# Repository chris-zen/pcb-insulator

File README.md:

# PCB Insulator

This project contains the design ideas to build a PCB insulator using UV LEDS.

The design is for a board of 100x75 mm, but you can compose several boards to increase the exposure surface. Just remember that you will need to use the appropriate power supply. I include some numbers to help with this.

# Numbers per board

LED specs: 3.3V 20mA

Voltage across resistor = 12V - (3 * 3.2V) = 2.4V

Resistor value = 2.4V / 0.02A = 120 Ohm

Power dissipated by resistor = 2.4V * 0.02A = 0.048 W = 48 mW

Power consumed by LED = 3.2V * 0.02A = 0.064W = 64mW

1 Board contains 16 resistors and 48 LEDs

Total power dissipated by resistors = 16 * 0.048W = 0.768W

Total power consumed by LEDs = 48 * 0.064W = 3.072W

**Total power = 0.768W + 3.072W = 3.84W**

**Total current consumption = 3.84W / 12V = 0.32A**

If you compose 4 boards you would need a power supply supporting 15.36W and 1.28A

# References

I have based my design on those other projects:

- http://www.instructables.com/id/Arduino-controlled-UV-LED-PCB-Exposure-Box/?ALLSTEPS
- http://www.carlolog.net/log/2012/09/making-an-uv-exposure-box-from-scratch/
- http://www.electronics-lab.com/project/led-uv-exposure-box/

# Part list

- [LEDs UV](https://www.amazon.es/gp/product/B01ANW9ZX2/ref=ox_sc_act_title_2?ie=UTF8&psc=1&smid=A1DMSD13LMYETC).
- [Power supply](https://www.amazon.es/gp/product/B01GC5QQ1I/ref=oh_aui_detailpage_o00_s01?ie=UTF8&psc=1)
- 100x75mm single layer PCB
- 120 Ohm 1/4W resistors

# Photos

https://goo.gl/photos/k7TKoiVqc2WFZSGJ9

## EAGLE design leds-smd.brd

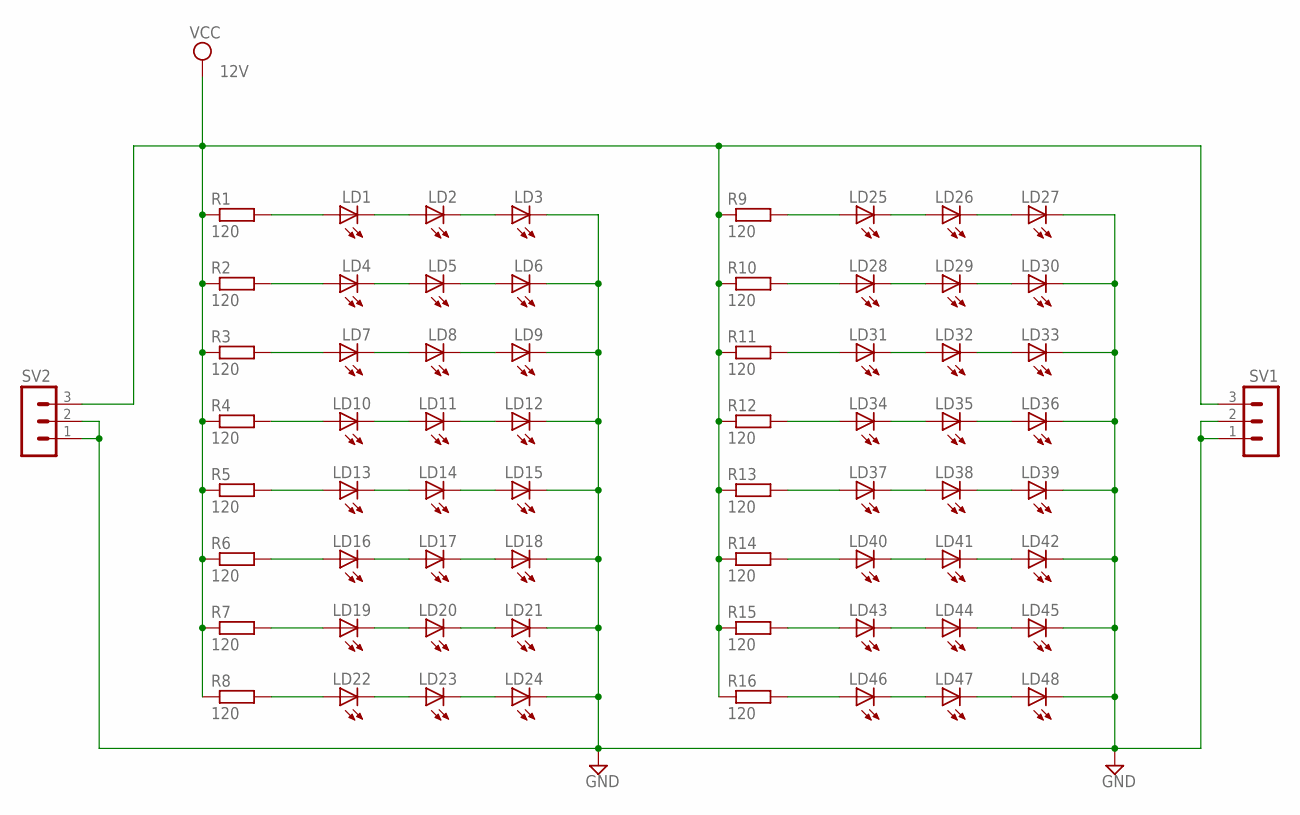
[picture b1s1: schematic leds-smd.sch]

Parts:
LD1, LD2, LD3, LD4, LD5, LD6, LD7, LD8, LD9, LD10, LD11, LD12, LD13, LD14, LD15, LD16, LD17, LD18, LD19, LD20, LD21, LD22, LD23, LD24, LD25, LD26, LD27, LD28, LD29, LD30, LD31, LD32, LD33, LD34, LD35, LD36, LD37, LD38, LD39, LD40, LD41, LD42, LD43, LD44, LD45, LD46, LD47, LD48: LED5MM
R1, R2, R3, R4, R5, R6, R7, R8, R9, R10, R11, R12, R13, R14, R15, R16: 120; M1206
SV1, SV2: MA03-1

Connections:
GND: LD3.K (C), LD6.K (C), LD9.K (C), LD12.K (C), LD15.K (C), LD18.K (C), LD21.K (C), LD24.K (C), LD27.K (C), LD30.K (C), LD33.K (C), LD36.K (C), LD39.K (C), LD42.K (C), LD45.K (C), LD48.K (C), SV1.1, SV1.2, SV2.1, SV2.2
unnamed: LD43.A, R15.2
unnamed: LD1.A, R1.2
unnamed: LD4.A, R2.2
unnamed: LD7.A, R3.2
unnamed: LD10.A, R4.2
unnamed: LD13.A, R5.2
unnamed: LD16.A, R6.2
unnamed: LD19.A, R7.2
unnamed: LD43.K (C), LD44.A
unnamed: LD1.K (C), LD2.A
unnamed: LD2.K (C), LD3.A
unnamed: LD5.K (C), LD6.A
unnamed: LD4.K (C), LD5.A
unnamed: LD7.K (C), LD8.A
unnamed: LD8.K (C), LD9.A
unnamed: LD44.K (C), LD45.A
unnamed: LD10.K (C), LD11.A
unnamed: LD11.K (C), LD12.A
unnamed: LD14.K (C), LD15.A
unnamed: LD13.K (C), LD14.A
unnamed: LD16.K (C), LD17.A
unnamed: LD17.K (C), LD18.A
unnamed: LD20.K (C), LD21.A
unnamed: LD19.K (C), LD20.A
unnamed: LD46.A, R16.2
unnamed: LD46.K (C), LD47.A
unnamed: LD22.A, R8.2
unnamed: LD25.A, R9.2
unnamed: LD28.A, R10.2
unnamed: LD31.A, R11.2
unnamed: LD34.A, R12.2
unnamed: LD37.A, R13.2
unnamed: LD40.A, R14.2
unnamed: LD22.K (C), LD23.A
unnamed: LD23.K (C), LD24.A
unnamed: LD26.K (C), LD27.A
unnamed: LD25.K (C), LD26.A
unnamed: LD28.K (C), LD29.A
unnamed: LD29.K (C), LD30.A
unnamed: LD32.K (C), LD33.A
unnamed: LD31.K (C), LD32.A
unnamed: LD34.K (C), LD35.A
unnamed: LD37.K (C), LD38.A
unnamed: LD40.K (C), LD41.A
unnamed: LD35.K (C), LD36.A
unnamed: LD38.K (C), LD39.A
unnamed: LD41.K (C), LD42.A
unnamed: LD47.K (C), LD48.A
VCC: R1.1, R2.1, R3.1, R4.1, R5.1, R6.1, R7.1, R8.1, R9.1, R10.1, R11.1, R12.1, R13.1, R14.1, R15.1, R16.1, SV1.3, SV2.3

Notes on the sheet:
12V

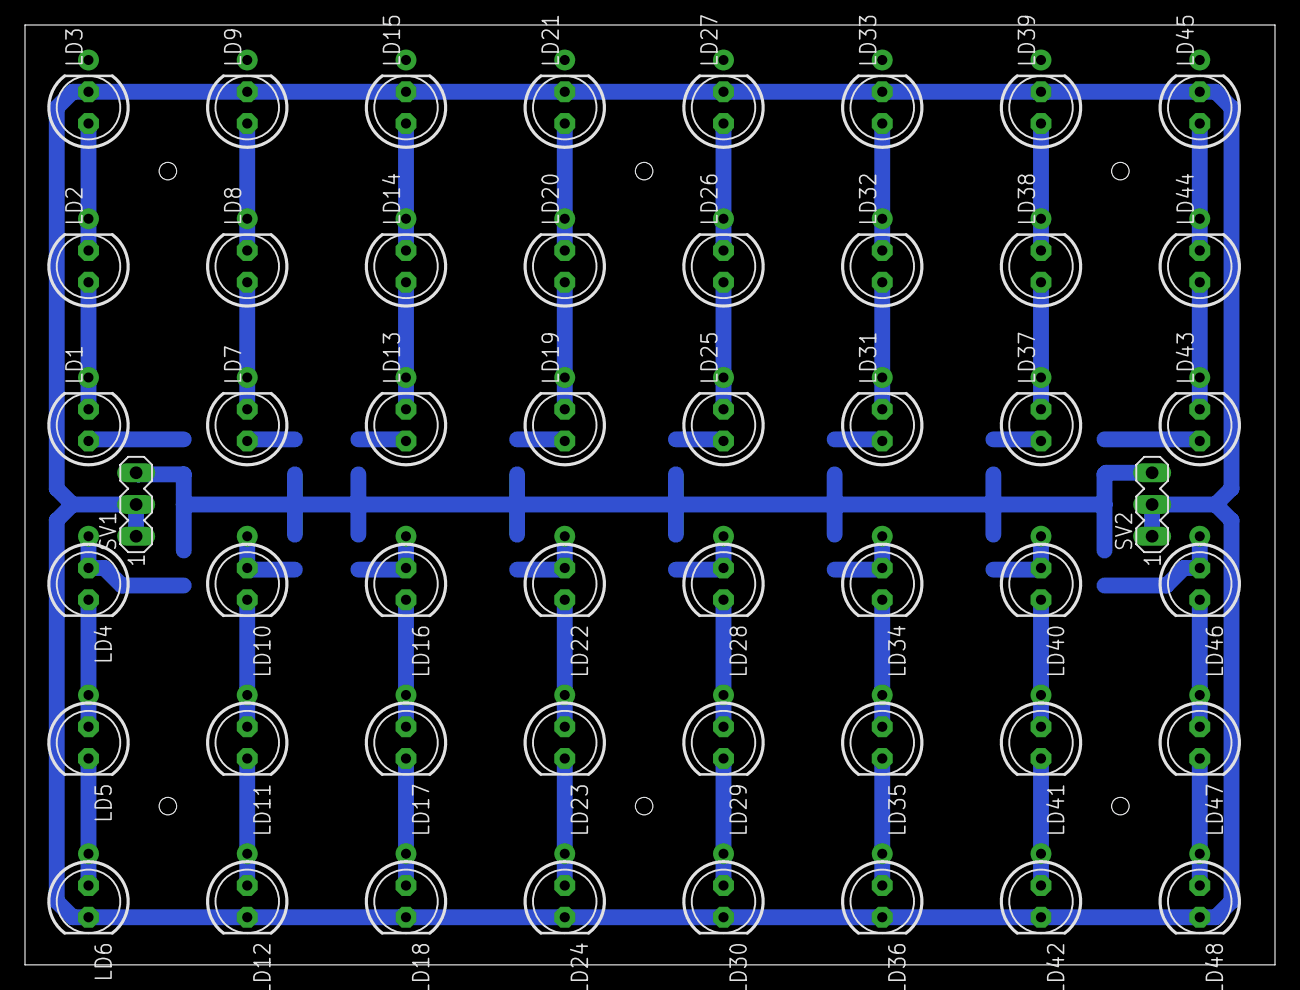
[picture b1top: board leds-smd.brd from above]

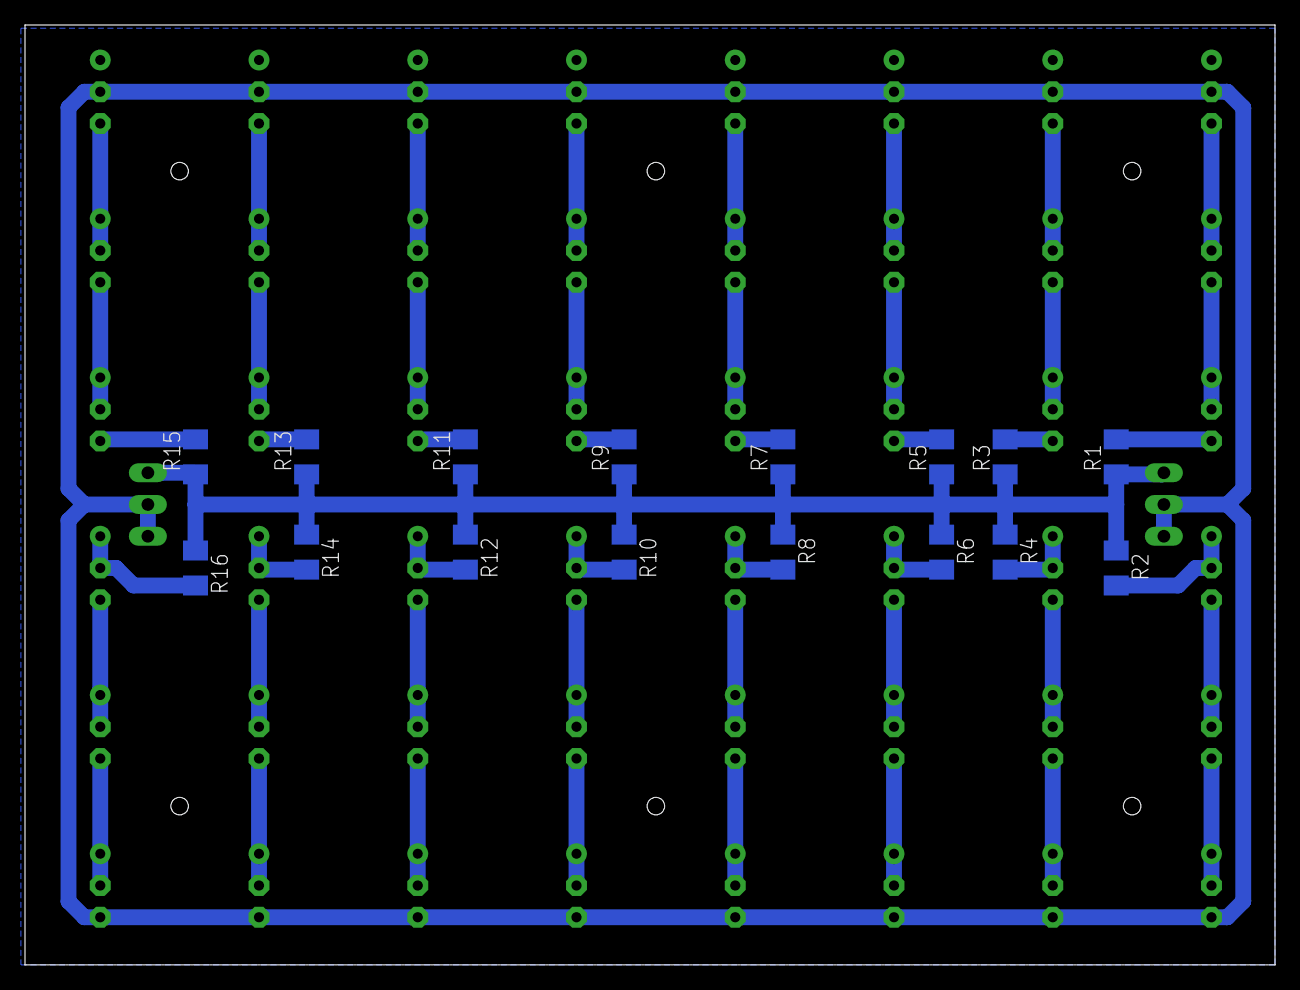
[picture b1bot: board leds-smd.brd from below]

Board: 2 copper layers, 100.0 x 75.2 mm, 66 parts (16 on the bottom side), 50 nets.

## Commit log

2017-03-12 Initial design
2017-03-12 Fixed new lines in README.md
2017-03-12 Updated part list
2017-03-12 Fixed docs and bottom-x4. Added SVG
2017-03-13 Added support for 5mm leds
2017-03-15 Added link to photos
